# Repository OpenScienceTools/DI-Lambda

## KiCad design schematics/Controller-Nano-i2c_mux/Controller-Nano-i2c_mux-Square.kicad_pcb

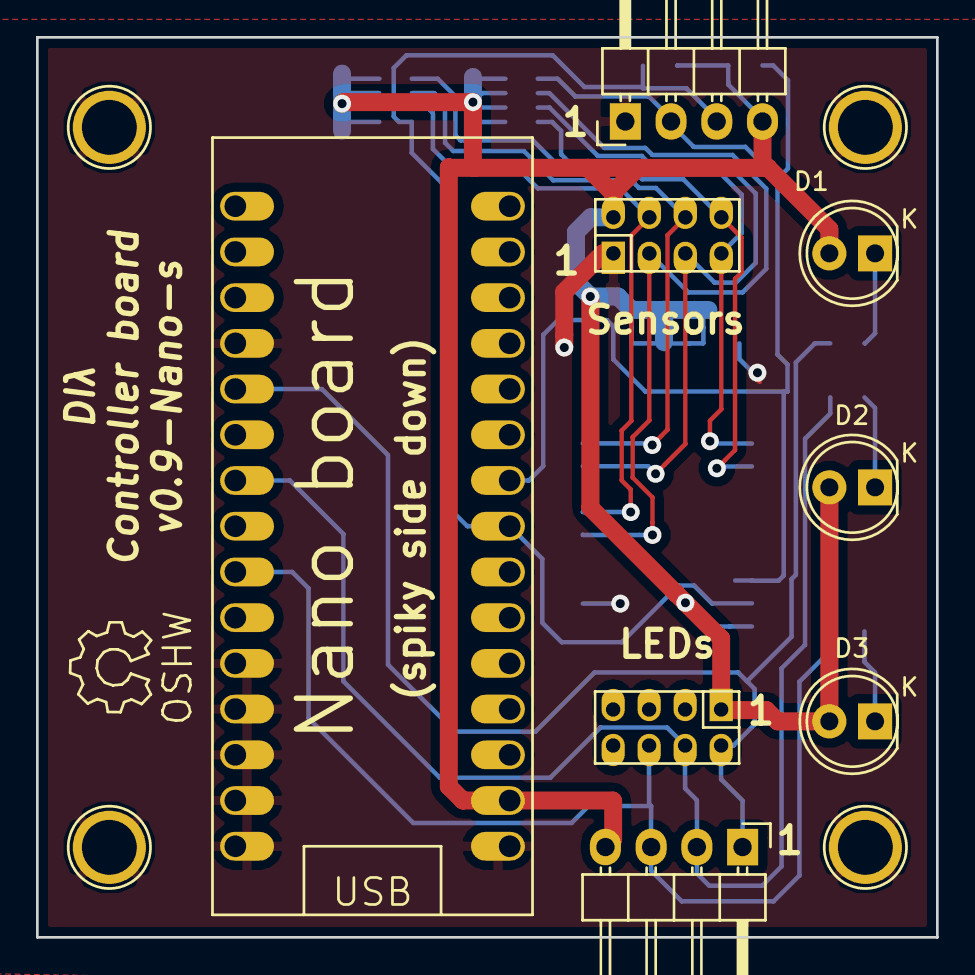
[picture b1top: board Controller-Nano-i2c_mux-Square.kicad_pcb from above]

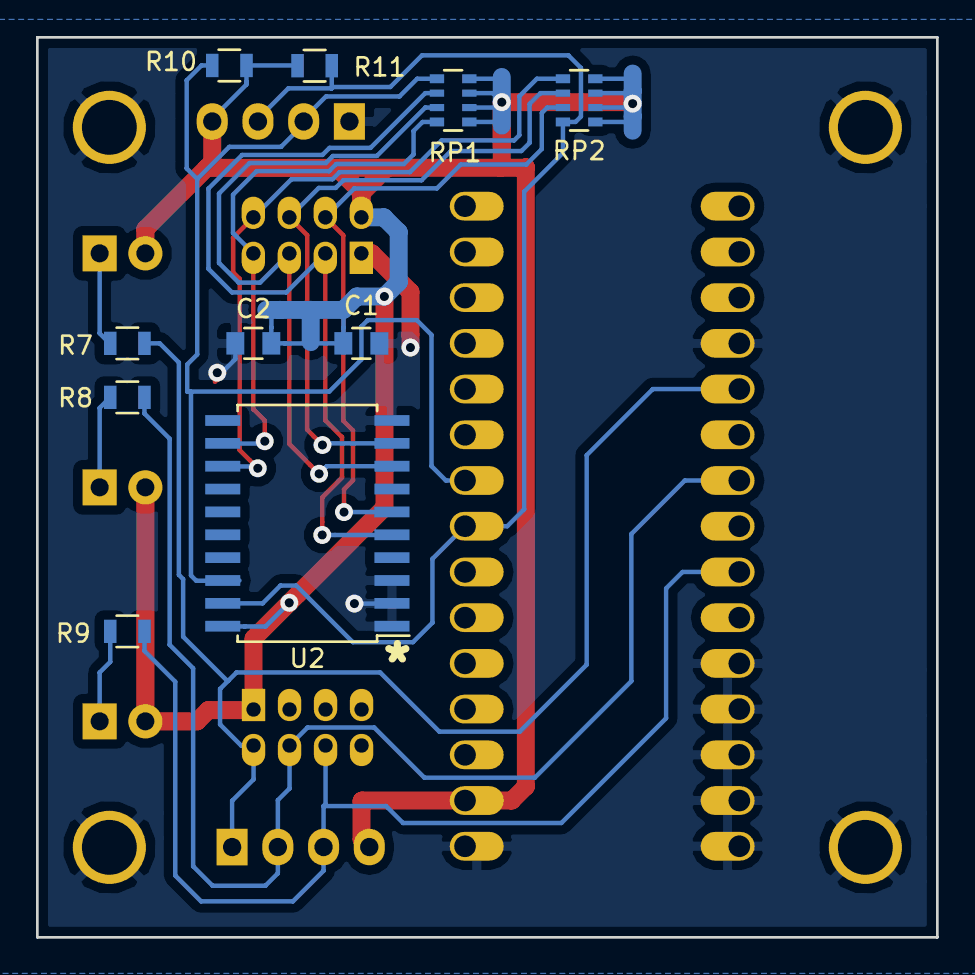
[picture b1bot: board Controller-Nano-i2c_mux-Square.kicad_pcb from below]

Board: 2 copper layers, 50.0 x 50.0 mm, 22 parts (10 on the bottom side), 16 nets.

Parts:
C1: 22nF; C_0805
C2: 1uF; C_0805
D1, D2, D3: LED; LED-5MM
P1, P2: CONN_02X04; Pin_Header_Straight_2x04_Pitch2.00mm
P3, P4: CONN_01X04; Pin_Header_Angled_1x04
P5, P6, P7, P8: CONN_01X01; 1pin
R7, R8, R9: 220; R_0805
R10, R11: 4k7; R_0805
RP1, RP2: R_PACK4; R_Array_Convex_4x0603
U1: Arduino_Nano; PDIP30-Nano
U2: PCA9544A; SOIC-20_7.5x12.8mm_Pitch1.27mm

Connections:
+3V3: C1.1, C2.1, D1.2, D2.2, D3.2, P1.2, P2.1, P3.4, P4.4, R10.2, R11.2, RP1.5, RP1.6, RP1.7, RP1.8, RP2.5, RP2.6, RP2.7, RP2.8, U1.17, U2.20
GND: C1.2, C2.2, P1.1, P4.1, P5.1, P6.1, P7.1, P8.1, U1.4, U1.11, U1.12, U1.13, U1.14, U1.15, U1.16, U2.1, U2.2, U2.3, U2.10
LED1: P2.2, P3.1, R7.2, U1.5
LED2: P2.4, P3.2, R8.2, U1.7
LED3: P2.6, P3.3, R9.2, U1.9
unnamed: D1.1, R7.1
unnamed: D2.1, R8.1
unnamed: D3.1, R9.1
SC0: P1.4, RP2.3, U2.6
SC1: P1.6, RP2.2, U2.9
SC2: P1.8, RP2.1, U2.13
SCL: P4.2, R10.1, RP1.1, U1.24, U2.18
SD0: P1.3, RP1.2, U2.5
SD1: P1.5, RP1.3, U2.8
SD2: P1.7, RP1.4, U2.12
SDA: P4.3, R11.1, RP2.4, U1.23, U2.19

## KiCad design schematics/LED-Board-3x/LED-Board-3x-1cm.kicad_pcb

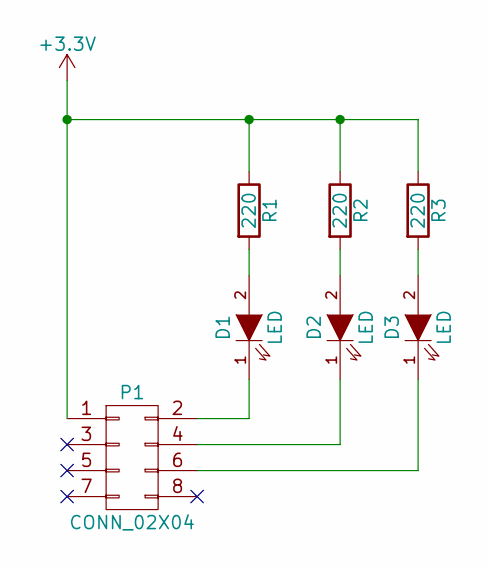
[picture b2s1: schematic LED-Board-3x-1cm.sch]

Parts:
D1, D2, D3: LED; LED-5MM
P1: CONN_02X04; Pin_Header_Straight_2x04_Pitch2.00mm
R1, R2, R3: 220; R_0805

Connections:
+3V3: P1.1, R1.1, R2.1, R3.1
unnamed: D1.1 (K), P1.2
unnamed: D1.2 (A), R1.2
unnamed: D2.1 (K), P1.4
unnamed: D2.2 (A), R2.2
unnamed: D3.1 (K), P1.6
unnamed: D3.2 (A), R3.2

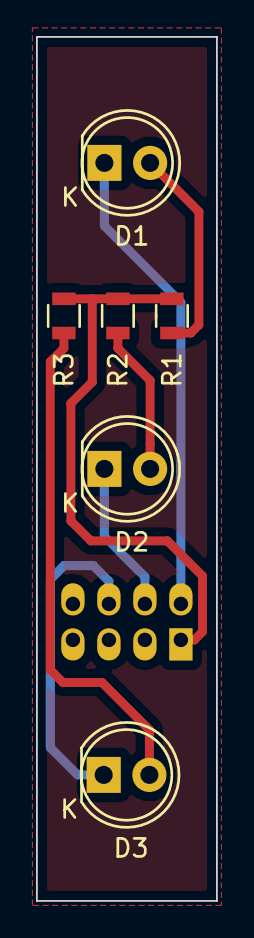
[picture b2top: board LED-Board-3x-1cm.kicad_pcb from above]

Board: 2 copper layers, 10.0 x 48.0 mm, 7 parts (1 on the bottom side), 7 nets.

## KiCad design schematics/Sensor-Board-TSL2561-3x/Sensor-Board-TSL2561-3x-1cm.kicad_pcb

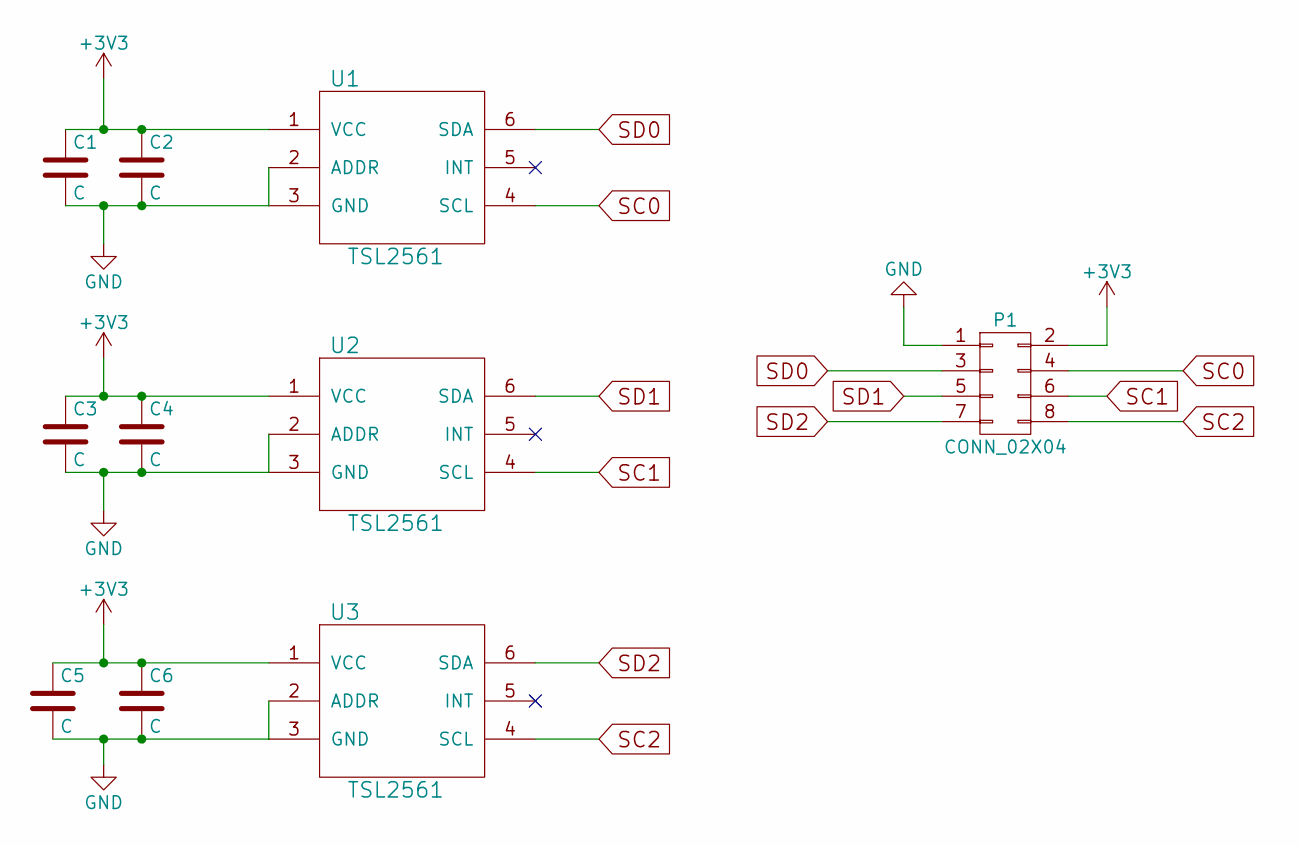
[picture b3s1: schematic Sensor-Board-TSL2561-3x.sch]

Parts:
C1, C2, C3, C4, C5, C6: C; C_0805
P1: CONN_02X04; Pin_Header_Straight_2x04_Pitch2.00mm
U1, U2, U3: TSL2561; TMB-6

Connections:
+3V3: C1.1, C2.1, C3.1, C4.1, C5.1, C6.1, P1.2, U1.1 (VCC), U2.1 (VCC), U3.1 (VCC)
GND: C1.2, C2.2, C3.2, C4.2, C5.2, C6.2, P1.1, U1.2 (ADDR), U1.3 (GND), U2.2 (ADDR), U2.3 (GND), U3.2 (ADDR), U3.3 (GND)
SC0: P1.4, U1.4 (SCL)
SC1: P1.6, U2.4 (SCL)
SC2: P1.8, U3.4 (SCL)
SD0: P1.3, U1.6 (SDA)
SD1: P1.5, U2.6 (SDA)
SD2: P1.7, U3.6 (SDA)

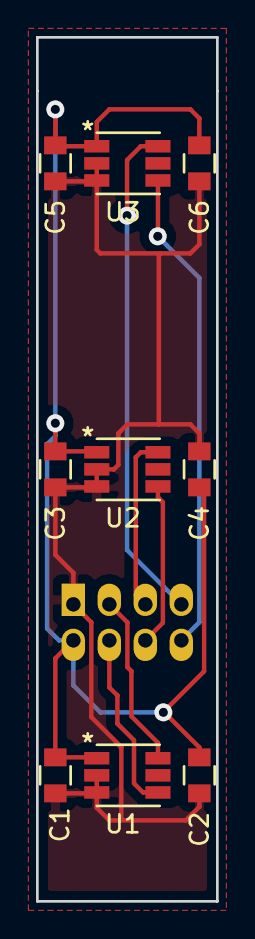
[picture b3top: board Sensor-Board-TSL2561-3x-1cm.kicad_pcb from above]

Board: 2 copper layers, 10.0 x 48.0 mm, 10 parts (1 on the bottom side), 8 nets.
